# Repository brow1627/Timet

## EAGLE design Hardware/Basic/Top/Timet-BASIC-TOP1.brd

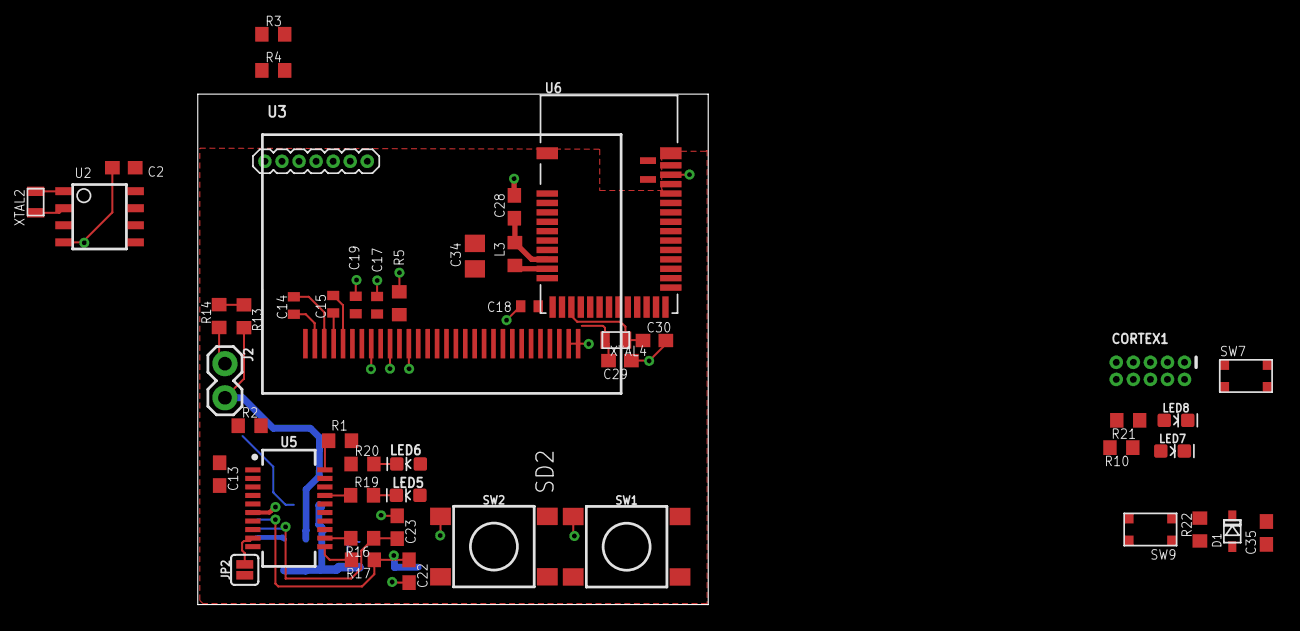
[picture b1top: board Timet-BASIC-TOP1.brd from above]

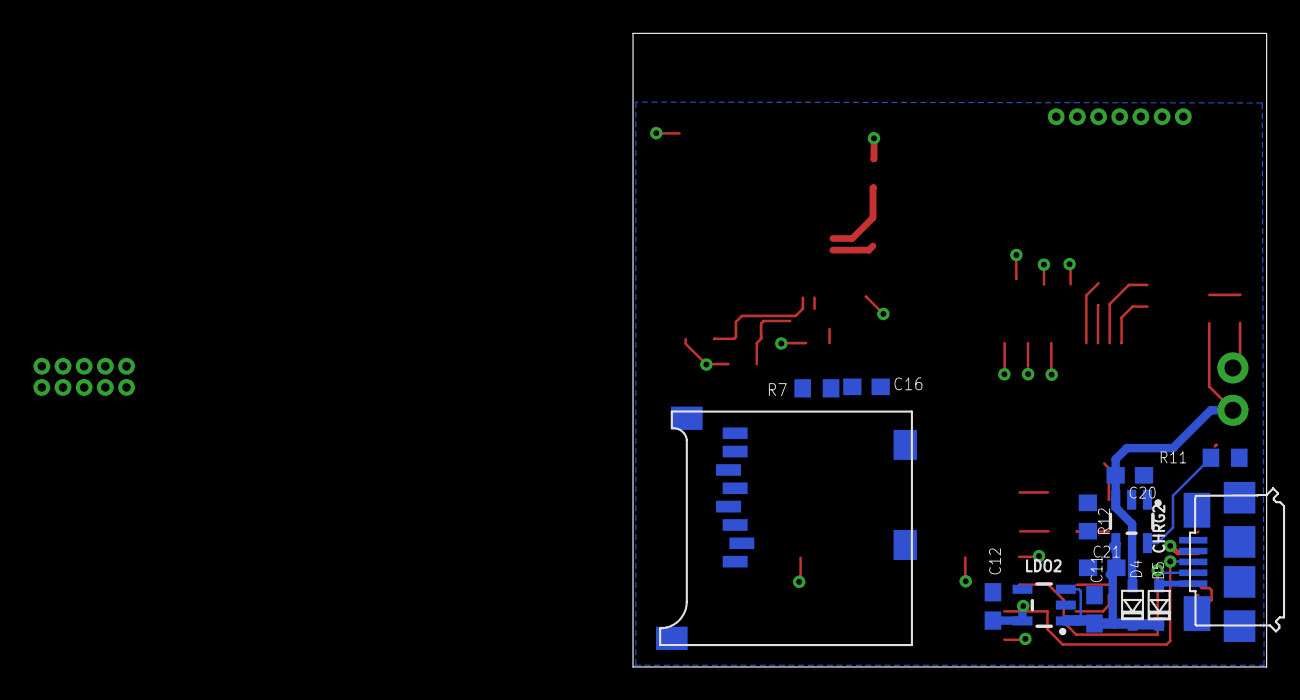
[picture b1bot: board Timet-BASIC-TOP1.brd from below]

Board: 2 copper layers, 38.0 x 38.0 mm, 62 parts (14 on the bottom side), 60 nets.

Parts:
C2, C11, C12, C28: 1u; C0603
C13, C35: 100n; C0603
C14, C15, C17, C18, C19: 2.2uF; C0402
C16: 10uF; C0603
C20, C21: 4.7u; C0603
C22, C23: 47p; C0603
C29, C30: C0603
C34: 10u; C0805
CHRG2: MCP73831; SOT23-5
CORTEX1: CORTEX_DEBUG_PTH; 2X5-PTH-1.27MM
D1, D4, D5: USC
J2: 1X02
J3: 1X07_1.27MM
JP2: SMT-JUMPER_2_NO_SILK
L3: 10u; L0603
LDO2: MIC5504; SOT23-5
LED5, LED7: RED; LED-0603
LED6: YELLOW; LED-0603
LED8: BLUE; LED-0603
R1, R2: 0; R0603
R3, R4, R5, R22: 10k; R0603
R7: 390k; R0603
R10, R19, R20, R21: 1k; R0603
R11: R0603
R12, R13, R14: 100k; R0603
R16, R17: 27; R0603
SD2: MICROSD
SW1, SW2: SWITCH.MOM; TACTILE_SWITCH_SMD_6.2MM_TALL
SW7, SW9: BUTTON-GULLWING
U2: PCF8523; SO8
U3: UG-2864HSWEG01_0.96IN_NO-WRAPAROUND
U5: FT231XS; SSOP20_L
U6: NRF52832_MODULE_MDBT42; BLE_MODULE_RAYTAC_MDBT42
USB2: USB.MICRO-BIGGERPADS; USB-MICRO-01.BIGGERPADS
XTAL2: 32.7680kHz; 2-SMD.NOLEAD.2.0MMTO1.2MM
XTAL4: 32.768kHz; 2-SMD.NOLEAD.2.0MMTO1.2MM

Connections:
3.3V: C2.1, C12.1, C13.2, C17.2, C19.2, C34.2, CORTEX1.1, D1.-, LDO2.5, LED5.A, LED6.A, R3.2, R4.2, R22.2, SD2.4, U2.8, U3.6, U3.9, U5.3, U5.14, U6.11
!CTS: JP2.2, U5.9
A4/BATT: R13.1, R14.2, U6.5
A6/TIA: J3.5, U6.7
A7/PPG: J3.7, U6.8
D3/RESET.OLED: U3.14, U6.16
D4/DC.OLED: U3.15, U6.17
D5/CD1: SD2.CD1, U6.18
D7/SD.CS: SD2.2, U6.20
D11/SW1: SW1.A1, U6.25
D15/SW2: SW2.A1, U6.29
D16/CS.OLED: U3.13, U6.30
D27/CHRG.STATUS: CHRG2.1, R12.1, U6.4
D29/LED.CTRL: J3.6, U6.6
DFU: SW7.3, U6.34
DTR: C35.1, U5.1
GND: C2.2, C11.1, C12.2, C13.1, C16.1, C17.1, C18.1, C19.1, C20.2, C21.1, C22.2, C23.1, C28.2, C29.1, C30.2, C34.1, CHRG2.2, CORTEX1.3, CORTEX1.5, CORTEX1.7, CORTEX1.9, J2.1, JP2.1, LDO2.2, LED7.C, LED8.C, R5.1, R7.2, R11.1, R14.1, SD2.6, SD2.MT1, SD2.MT2, SW1.B1, SW1.B2, SW2.B1, SW2.B2, SW7.1, SW9.3, U2.4, U3.1, U3.8, U3.10, U3.12, U3.29, U3.30, U5.6, U5.16, U6.1, U6.12, U6.24, U6.39, USB2.5, USB2.S1, USB2.S2, USB2.S3, USB2.S4, USB2.S5, USB2.S6
LED1: R10.2, U6.31
LED2: R21.2, U6.33
MISO: SD2.7, U6.28
MOSI: SD2.3, U3.19, U6.27
unnamed: U2.2, XTAL2.P$1
unnamed: R5.2, U3.11
unnamed: U2.1, XTAL2.P$2
unnamed: R7.1, U3.26
unnamed: C14.2, U3.2
unnamed: C14.1, U3.3
unnamed: C15.2, U3.4
unnamed: C15.1, U3.5
unnamed: C16.2, U3.28
unnamed: C18.2, U3.27
unnamed: CHRG2.5, R11.2
unnamed: R16.2, U5.12
unnamed: R17.2, U5.11
unnamed: LED5.C, R19.2
unnamed: LED6.C, R20.2
unnamed: C29.2, U6.13, XTAL4.P$1
unnamed: C30.1, U6.14, XTAL4.P$2
unnamed: LED7.A, R10.1
unnamed: LED8.A, R21.1
unnamed: L3.1, U6.10
unnamed: C28.1, L3.2, U6.9
RESET: C35.2, CORTEX1.10, D1.+, R22.1, SW9.1, U6.35
RXD.FT: R2.1, U5.4
RXD.NRF: R1.2, U6.21
RXLED: R19.1, U5.17
SCK: SD2.5, U3.18, U6.26
SCL: R4.1, U2.6, U6.3
SDA: R3.1, U2.5, U6.2
SWCLK: CORTEX1.4, U6.36
SWDIO: CORTEX1.2, U6.37
SWO: CORTEX1.6, U6.32
TXD.FT: R1.1, U5.20
TXD.NRF: R2.2, U6.19
TXLED: R20.1, U5.10
USB+: C22.1, R17.1, USB2.3
USB-: C23.2, R16.1, USB2.2
VIN: C11.2, C21.2, CHRG2.4, D4.-, D5.-, LDO2.1, LDO2.3, R12.2
VLIPO: C20.1, CHRG2.3, D4.+, J2.2, R13.2
V_USB: D5.+, U5.15, USB2.1

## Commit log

2020-07-01 Initializing Guidelines
2020-07-13 adding folders part 2
2020-07-13 removed files stored in incorrect location
